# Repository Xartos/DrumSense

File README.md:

# DrumSense
Drum triggered LEDs with electrical schematics.

The circuitboard is drawn in KiCad and the code is written using Atmel Studio.

# Disclaimer
This is my first project shared to github so bare with me

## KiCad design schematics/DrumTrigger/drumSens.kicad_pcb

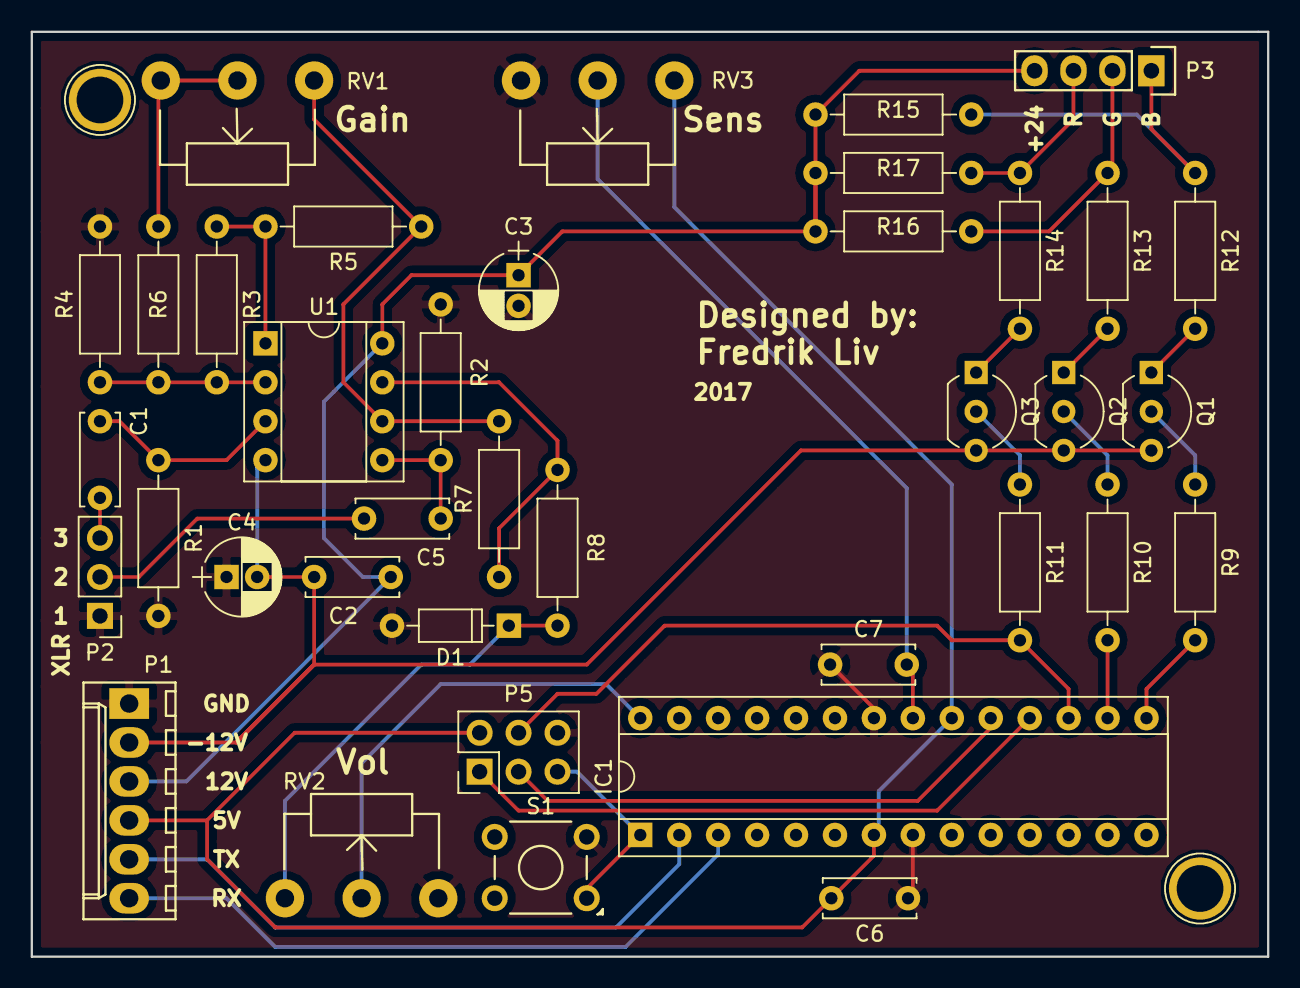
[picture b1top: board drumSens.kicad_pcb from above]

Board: 2 copper layers, 80.6 x 60.3 mm, 38 parts (0 on the bottom side), 33 nets.

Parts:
C1, C2, C5, C6, C7: 100nf; C_Disc_D6.0mm_W2.5mm_P5.00mm
C3, C4: 10µF; CP_Radial_D5.0mm_P2.00mm
D1: 5V; D_DO-35_SOD27_P7.62mm_Horizontal
IC1: ATMEGA328P-P; DIP-28_W7.62mm_Socket
P1: CONN_01X06; Molex_KK-6410-06_06x2.54mm_Straight
P2: CONN_01X03; Pin_Header_Straight_1x03_Pitch2.54mm
P3: CONN_01X04; Socket_Strip_Straight_1x04
P5: CONN_02X03; Pin_Header_Straight_2x03_Pitch2.54mm
Q1, Q2, Q3: 2N3904; TO-92_Inline_Wide
R1, R2, R3, R4, R5, R7, R8, R15, R16, R17: 10k; R_Axial_DIN0207_L6.3mm_D2.5mm_P10.16mm_Horizontal
R6, R9, R10, R11, R12, R13, R14: 220; R_Axial_DIN0207_L6.3mm_D2.5mm_P10.16mm_Horizontal
RV1: 10k; Potentiometer_WirePads_largePads(Flipped)
RV2: 10k; Potentiometer_WirePads_largePads
RV3: 10k; Potentiometer_WirePads
S1: TAC_SWITCH; SW_TH_Tactile_Omron_B3F-10xx
U1: NE5532; DIP-8_W7.62mm_Socket

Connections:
GND: C3.2, C4.1, C6.1, C7.1, D1.2, IC1.8, IC1.22, P1.1, P2.1, P5.6, R1.2, R2.2, R4.2, RV2.3, RV3.3, S1.3
unnamed: C1.1, R1.1, U1.3
unnamed: C1.2, P2.3
unnamed: C2.1, R2.1, U1.5
unnamed: C2.2, P2.2
unnamed: C3.1, C5.2, P1.3, P3.4, R15.2, R16.2, R17.2, U1.8
unnamed: C4.2, C5.1, P1.2, Q1.3, Q2.3, Q3.3, U1.4
unnamed: C6.2, IC1.7, IC1.20, P1.4, P5.2, RV3.1
unnamed: C7.2, IC1.21, RV3.2
unnamed: D1.1, R8.1, RV2.1
unnamed: IC1.1, P5.5, S1.1
unnamed: IC1.2, P1.5
unnamed: IC1.3, P1.6
unnamed: IC1.15, R9.2
unnamed: IC1.16, R10.2
unnamed: IC1.17, P5.4, R11.2
unnamed: IC1.18, P5.1
unnamed: IC1.19, P5.3
unnamed: IC1.28, RV2.2
unnamed: P3.1, R12.1, R15.1
unnamed: P3.2, R13.1, R16.1
unnamed: P3.3, R14.1, R17.1
unnamed: Q1.1, R12.2
unnamed: Q1.2, R9.1
unnamed: Q2.1, R13.2
unnamed: Q2.2, R10.1
unnamed: Q3.1, R14.2
unnamed: Q3.2, R11.1
unnamed: R3.1, R5.2, U1.1
unnamed: R3.2, R4.1, R6.2, U1.2
unnamed: R5.1, R7.2, RV1.3, U1.6
unnamed: R6.1, RV1.1, RV1.2
unnamed: R7.1, R8.2, U1.7

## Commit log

2017-02-14 Added current content
2017-02-14 Deleted compiled files
2017-02-14 Changed gitignore to ignore compiled files
2017-02-14 Added gerberfiles
2017-02-14 Typo fix
2017-02-15 Added controller schematics and moved trigger schematic, same with code
2017-02-16 Changed .gitignore to match new file structure
2017-02-16 Added start on UART bus functionality
2017-02-16 Changed callback function and added ACK/NACK functionality
2017-02-20 Change uart state to enum and added todo
